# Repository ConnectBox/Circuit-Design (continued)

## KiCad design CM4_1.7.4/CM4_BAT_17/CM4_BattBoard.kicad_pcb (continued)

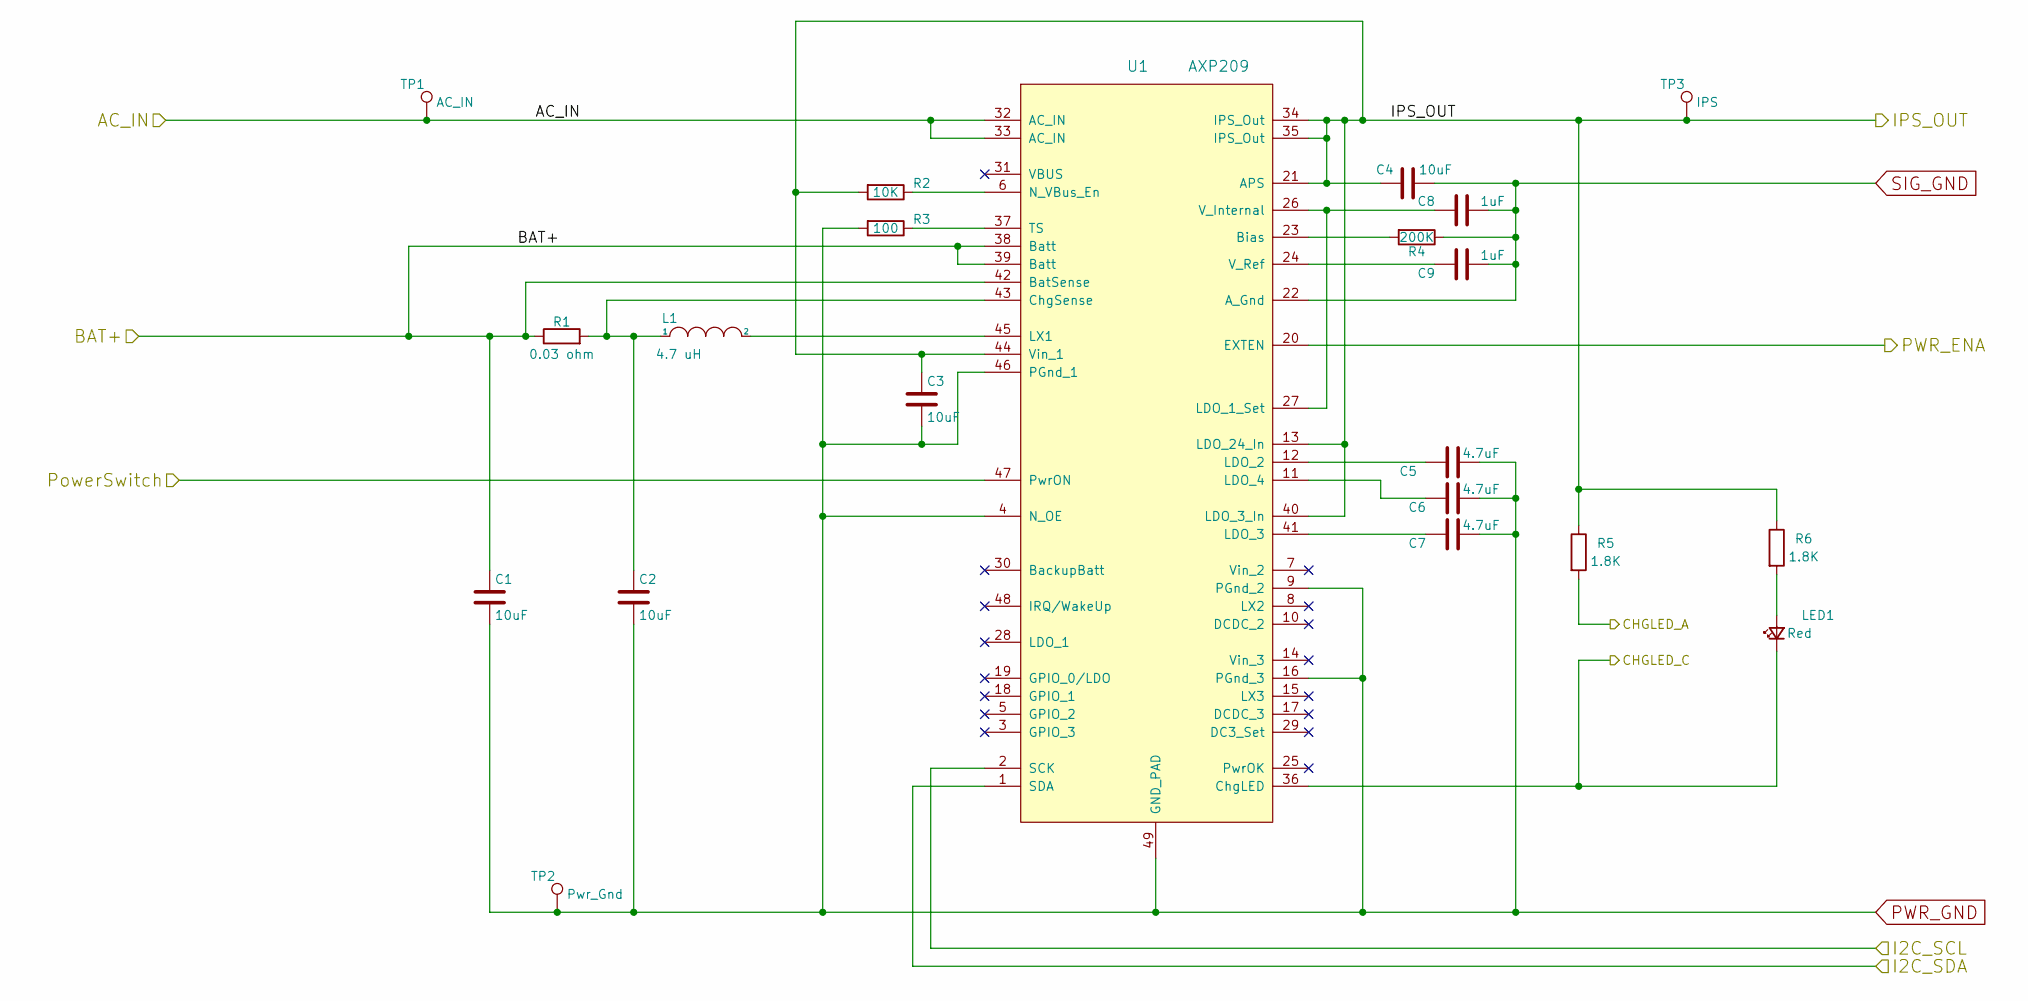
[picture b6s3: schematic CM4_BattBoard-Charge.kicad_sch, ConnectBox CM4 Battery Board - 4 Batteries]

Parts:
C1, C2, C3, C4: 10uF; C_0603_1608Metric; Manufacturer P/N C0603C106M9PACTU; DigiKey P/N 399-5504-1-ND
C5, C6, C7: 4.7uF; C_0603_1608Metric; Manufacturer P/N C0603C475K9PACTU; DigiKey P/N 399-3482-1-ND
C8, C9: 1uF; C_0603_1608Metric; Manufacturer P/N C0603C105K9PACTU; DigiKey P/N 399-7848-1-ND
L1: 4.7 uH; INDUCTOR_SMD_6x6-1; Manufacturer P/N NR6028T4R7M; DigiKey P/N 587-2100-1-ND
LED1: Red; LED_0603_1608Metric; Manufacturer P/N LTST-C191KRKT; DigiKey P/N 160-1447-1-ND
R1: 0.03 ohm; R_0805_2012Metric; Manufacturer P/N ERJ-6CWFR030V; DigiKey P/N P19207CT-ND
R2: 10K; R_0603_1608Metric; Manufacturer P/N RC0603FR-0710KL; DigiKey P/N 311-10.0KHRCT-ND
R3: 100; R_0603_1608Metric; Manufacturer P/N RC06-3FR-07100RL; DigiKey P/N 311-100HRCT-ND
R4: 200K; R_0603_1608Metric; Manufacturer P/N RC0603FR-07200KL; DigiKey P/N 311-200KHRCT-ND
R5, R6: 1.8K; R_0603_1608Metric; Manufacturer P/N RC0603FR-071K8L; DigiKey P/N 311-1.80KHRCT-ND
TP1: AC_IN; TestPoint_THTPad_D1.5mm_Drill0.7mm
TP2: Pwr_Gnd; TestPoint_THTPad_D1.5mm_Drill0.7mm
TP3: IPS; TestPoint_THTPad_D1.5mm_Drill0.7mm
U1: AXP209; UQFN-48-1EP_6x6mm_Pitch0.4mm_75; Manufacturer P/N AXP209

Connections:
/AC_IN: TP1.1, U1.32 (AC_IN), U1.33 (AC_IN); also elsewhere on the board
/CHGLED_A: R5.2; also elsewhere on the board
/CHGLED_C: LED1.1 (K), U1.36 (ChgLED); also elsewhere on the board
/Charge control/IPS_OUT: C3.1, C4.1, R2.2, R5.1, R6.1, TP3.1, U1.13 (LDO_24_In), U1.21 (APS), U1.34 (IPS_Out), U1.35 (IPS_Out), U1.40 (LDO_3_In), U1.44 (Vin_1); also elsewhere on the board
/I2C_SCL: U1.2 (SCK); also elsewhere on the board
/I2C_SDA: U1.1 (SDA); also elsewhere on the board
/PWR_ENA: U1.20 (EXTEN); also elsewhere on the board
/PowerSwitch: U1.47 (PwrON); also elsewhere on the board
unnamed: C2.1, L1.1, R1.2, U1.43 (ChgSense)
unnamed: C5.2, U1.12 (LDO_2)
unnamed: C6.2, U1.11 (LDO_4)
unnamed: C7.2, U1.41 (LDO_3)
unnamed: C8.2, U1.26 (V_Internal), U1.27 (LDO_1_Set)
unnamed: C9.2, U1.24 (V_Ref)
unnamed: L1.2, U1.45 (LX1)
unnamed: LED1.2 (A), R6.2
unnamed: R2.1, U1.6 (N_VBus_En)
unnamed: R3.1, U1.37 (TS)
unnamed: R4.2, U1.23 (Bias)
PWR_GND: C1.2, C2.2, C3.2, C5.1, C6.1, C7.1, R3.2, TP2.1, U1.4 (N_OE), U1.9 (PGnd_2), U1.16 (PGnd_3), U1.46 (PGnd_1), U1.49 (GND_PAD); also elsewhere on the board
SIG_GND: C4.2, C8.1, C9.1, R4.1, U1.22 (A_Gnd); also elsewhere on the board

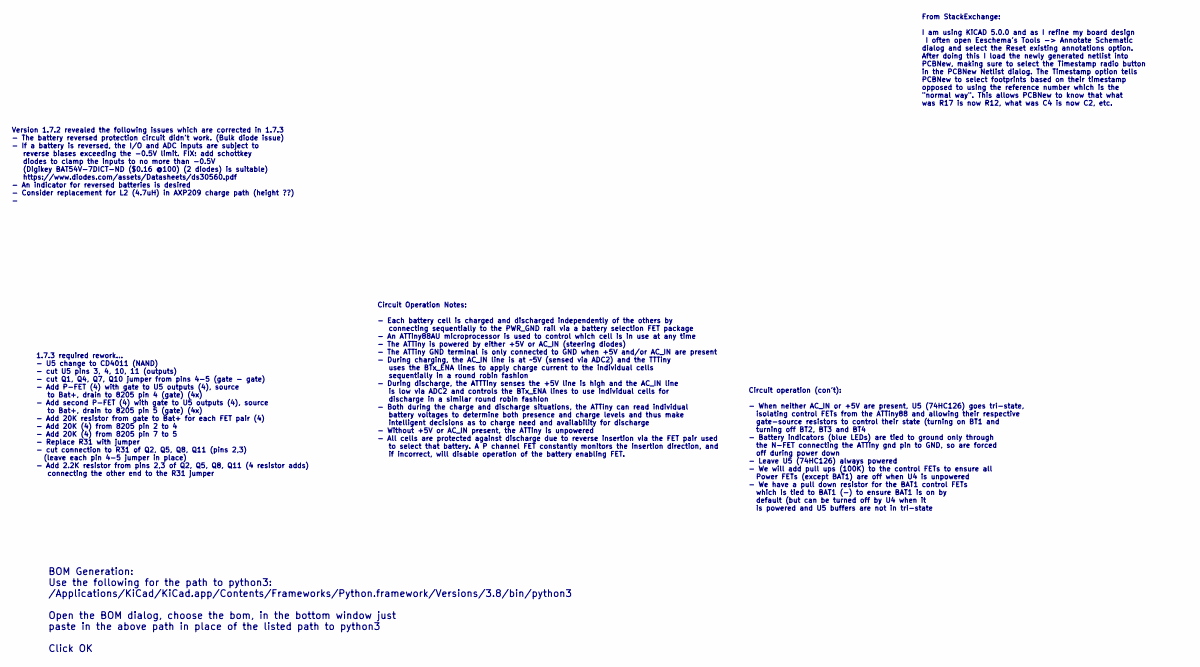
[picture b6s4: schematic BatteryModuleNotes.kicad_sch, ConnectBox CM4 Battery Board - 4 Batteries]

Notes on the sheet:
Version 1.7.2 revealed the following issues which are corrected in 1.7.3 - The battery reversed protection circuit didn't work. (Bulk diode issue) - If a battery is reversed, the I/O and ADC inputs are subject to reverse biases exceeding the -0.5V limit. FIX: add schottkey diodes to clamp the input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
1.7.3 required rework... - U5 change to CD4011 (NAND) - cut U5 pins 3, 4, 10, 11 (outputs) - cut Q1, Q4, Q7, Q10 jumper from pins 4-5 (gate - gate) - Add P-FET (4) with gate to U5 outputs (4), source to Bat+, drain to 8205 pin 4 (gate) (4x) - Add second P-FET (4) with gate to U5 outputs (4), source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
BOM Generation: Use the following for the path to python3: /Applications/KiCad/KiCad.app/Contents/Frameworks/Python.framework/Versions/3.8/bin/python3 Open the BOM dialog, choose the bom, in the bottom window just paste in the above path in place of the listed path to python3 Click OK
Circuit Operation Notes: - Each battery cell is charged and discharged independently of the others by connecting sequentially to the PWR_GND rail via a battery selection FET package - An ATTiny88AU microprocessor is used to control which cell is in use at any time - The ATTiny is powered by either 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
Circuit operation (con't): - When neither AC_IN or +5V are present, U5 (74HC126) goes tri-state, isolating control FETs from the ATTiny88 and allowing their respective gate-source resistors to control their state (turning on BT1 and turning off BT2, BT3 and BT4 - Battery indicators (blue LEDs) are 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
From StackExchange: I am using KiCAD 5.0.0 and as I refine my board design I often open Eeschema's Tools -> Annotate Schematic dialog and select the Reset existing annotations option. After doing this I load the newly generated netlist into PCBNew, making sure to select the Timestamp radio button i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

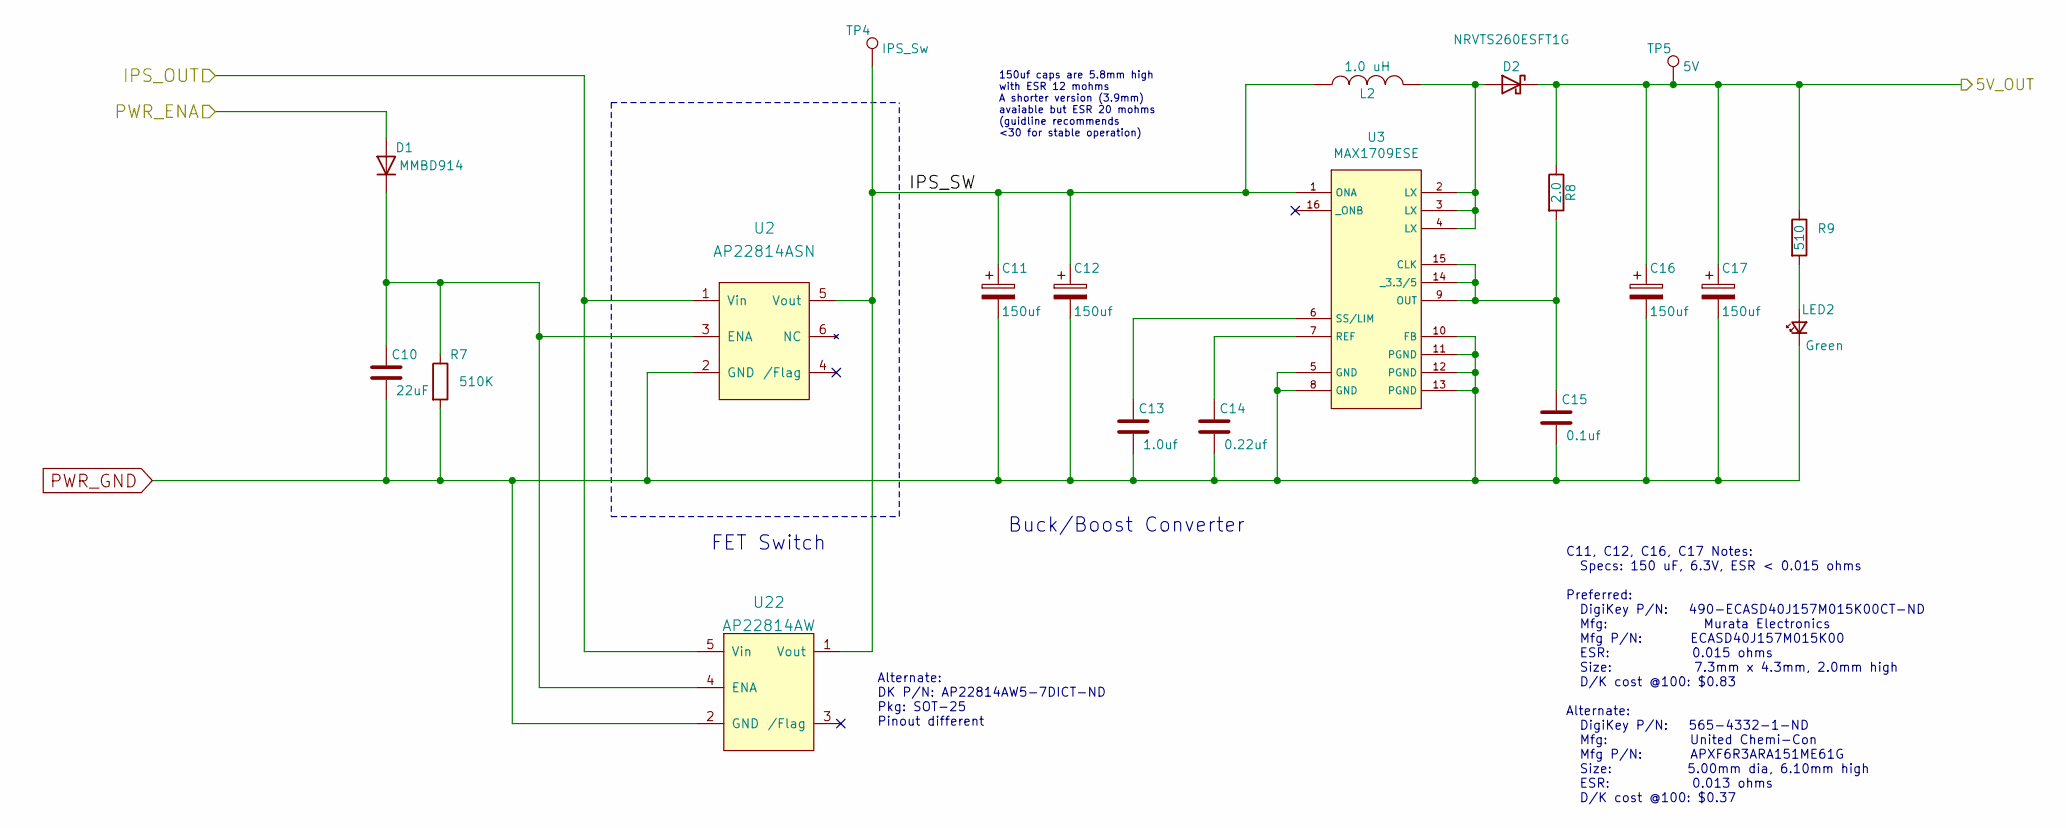
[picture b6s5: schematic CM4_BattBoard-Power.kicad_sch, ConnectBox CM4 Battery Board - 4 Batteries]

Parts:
C10: 22uF; C_0603_1608Metric; Manufacturer P/N CL10A226MQ8NRNC; DigiKey P/N 1276-1193-1-ND
C11, C12, C16, C17: 150uf; CAP_ECAS_SMD_dual; Manufacturer P/N ECASD40J157M015K00; DigiKey P/N 490-ECASD40J157M015K00CT-ND
C13: 1.0uf; C_0603_1608Metric; Manufacturer P/N C0603C105K9PACTU; DigiKey P/N 399-7848-1-ND
C14: 0.22uf; C_0603_1608Metric; Manufacturer P/N C0603C224K9PAC7867; DigiKey P/N 399-14969-1-ND
C15: 0.1uf; C_0603_1608Metric; Manufacturer P/N C0603C104K9PAC7867; DigiKey P/N 399-17575-1-ND
D1: MMBD914; D_SOT-23_ANK; Manufacturer P/N MMBD914LT1G; DigiKey P/N MMBD914LT1GOSCT-ND
D2: NRVTS260ESFT1G; SOD-123FL; Manufacturer P/N NRVTS260ESFT1G; DigiKey P/N NRVTS260ESFT1GOSCT-ND
L2: 1.0 uH; L_Taiyo-Yuden_MD-5050; Manufacturer P/N LQH5BPN1R0N38L; DigiKey P/N 490-16290-1-ND
LED2: Green; LED_0603_1608Metric; Manufacturer P/N LTST-C191KFKT; DigiKey P/N 160-1446-1-ND
R7: 510K; R_0603_1608Metric; Manufacturer P/N RC0603FR-07510KL; DigiKey P/N 311-510KHRCT-ND
R8: 2.0; R_0603_1608Metric; Manufacturer P/N RC0603FR-072RL; DigiKey P/N 311-2.00HRCT-ND
R9: 510; R_0603_1608Metric; Manufacturer P/N RC0603FR-07510RL; DigiKey P/N 311-510RHRCT-ND
TP4: IPS_Sw; TestPoint_THTPad_D1.5mm_Drill0.7mm
TP5: 5V; TestPoint_THTPad_D1.5mm_Drill0.7mm
U2: AP22814ASN; U-DFN2020-6; Manufacturer P/N AP22814ASN-7; DigiKey P/N AP22814ASN-7DICT-ND
U3: MAX1709ESE; SOP-16_3.9x9.9mm_P1.27mm; Manufacturer P/N MAX1709ESE
U22: AP22814AW; SOT-23-5; Manufacturer P/N AP22814AW5-7; DigiKey P/N AP22814AW5-7DICT-ND

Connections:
/+5V: C16.1, C17.1, D2.1 (K), R8.1, R9.1, TP5.1; also elsewhere on the board
/Charge control/IPS_OUT: U2.1 (Vin), U22.5 (Vin); also elsewhere on the board
/PWR_ENA: D1.2 (A); also elsewhere on the board
/Power/IPS_SW: C11.1, C12.1, L2.1, TP4.1, U2.5 (Vout), U3.1 (ONA), U22.1 (Vout)
unnamed: C10.1, D1.1 (K), R7.1, U2.3 (ENA), U22.4 (ENA)
unnamed: C13.1, U3.6 (SS/LIM)
unnamed: C14.1, U3.7 (REF)
unnamed: C15.1, R8.2, U3.9 (OUT), U3.14 (_3.3/5), U3.15 (CLK)
unnamed: D2.2 (A), L2.2, U3.2 (LX), U3.3 (LX), U3.4 (LX)
unnamed: LED2.2 (A), R9.2
PWR_GND: C10.2, C11.2, C12.2, C13.2, C14.2, C15.2, C16.2, C17.2, LED2.1 (K), R7.2, U2.2 (GND), U3.5 (GND), U3.8 (GND), U3.10 (FB), U3.11 (PGND), U3.12 (PGND), U3.13 (PGND), U22.2 (GND); also elsewhere on the board

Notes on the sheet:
FET Switch
Alternate: DK P/N: AP22814AW5-7DICT-ND Pkg: SOT-25 Pinout different
150uf caps are 5.8mm high with ESR 12 mohms A shorter version (3.9mm) avaiable but ESR 20 mohms (guidline recommends <30 for stable operation)
Buck/Boost Converter
C11, C12, C16, C17 Notes: Specs: 150 uF, 6.3V, ESR < 0.015 ohms Preferred: DigiKey P/N: 490-ECASD40J157M015K00CT-ND Mfg: Murata Electronics Mfg P/N: ECASD40J157M015K00 ESR: 0.015 ohms Size: 7.3mm x 4.3mm, 2.0mm high D/K cost @100: $0.83 Alternate: DigiKey P/N: 565-4332-1-ND Mfg: United Chemi-Con Mf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

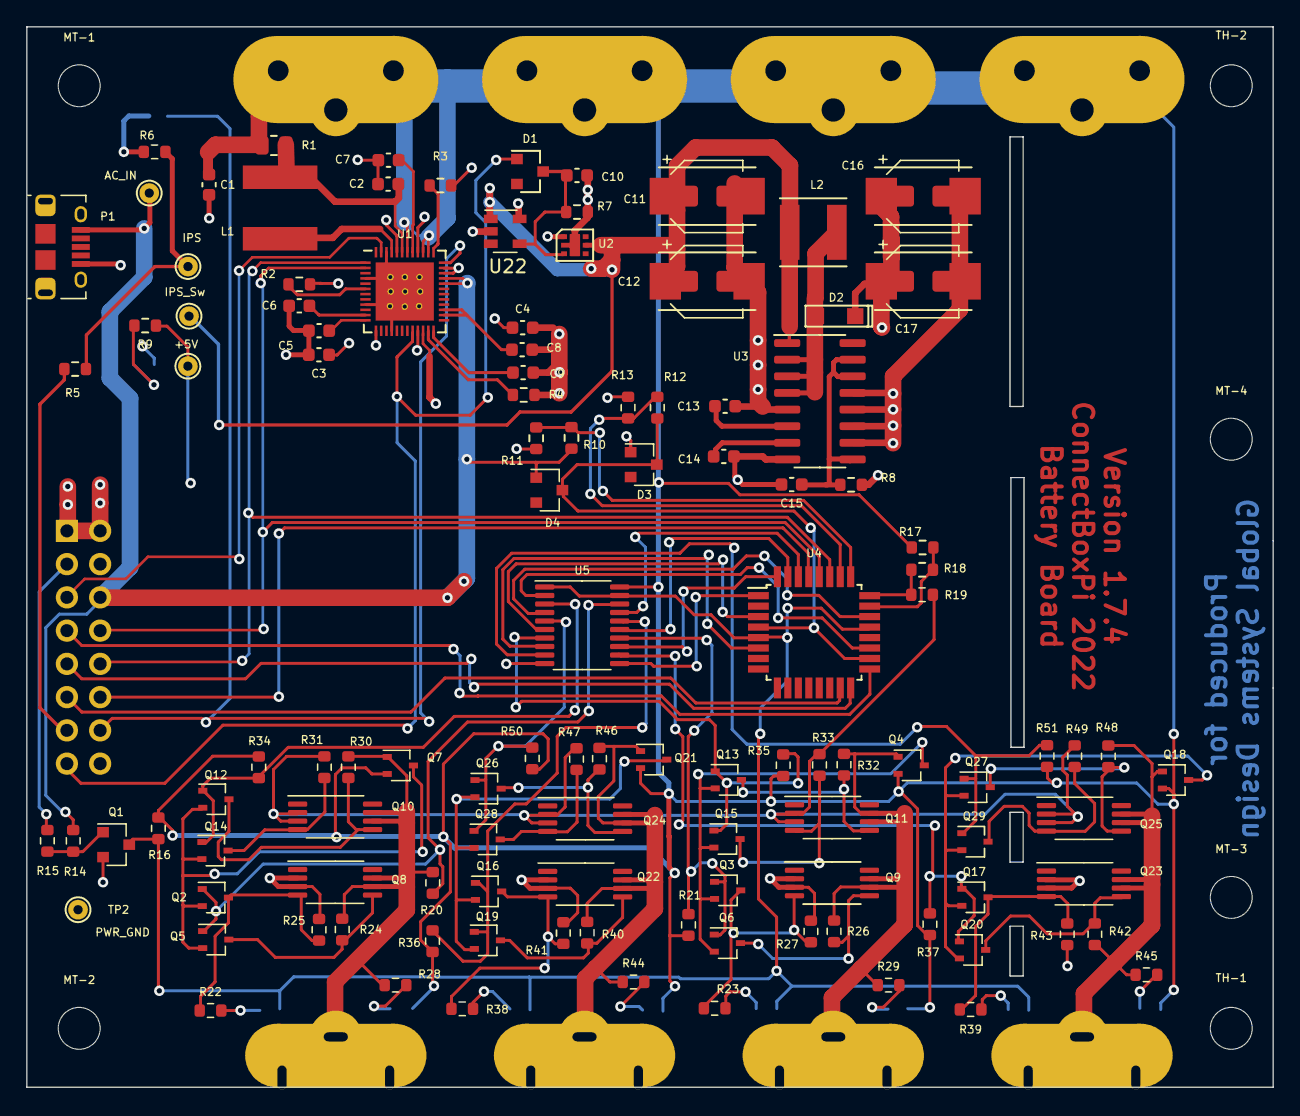
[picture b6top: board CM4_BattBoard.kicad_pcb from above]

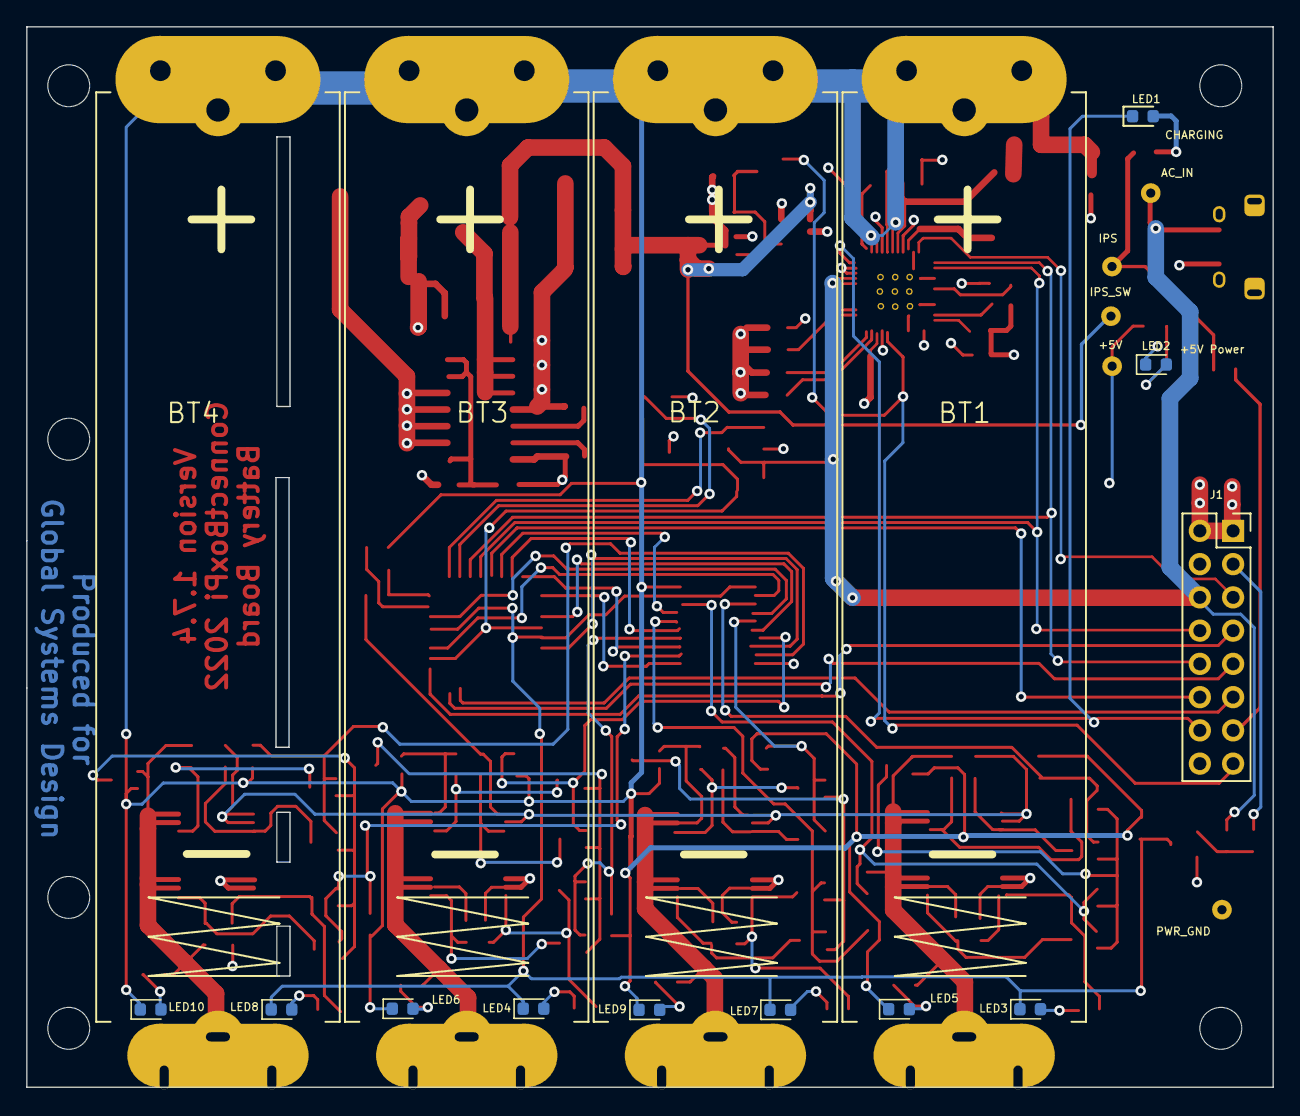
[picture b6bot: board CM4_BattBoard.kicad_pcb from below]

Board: 4 copper layers, 95.2 x 81.0 mm, 136 parts (15 on the bottom side), 90 nets.

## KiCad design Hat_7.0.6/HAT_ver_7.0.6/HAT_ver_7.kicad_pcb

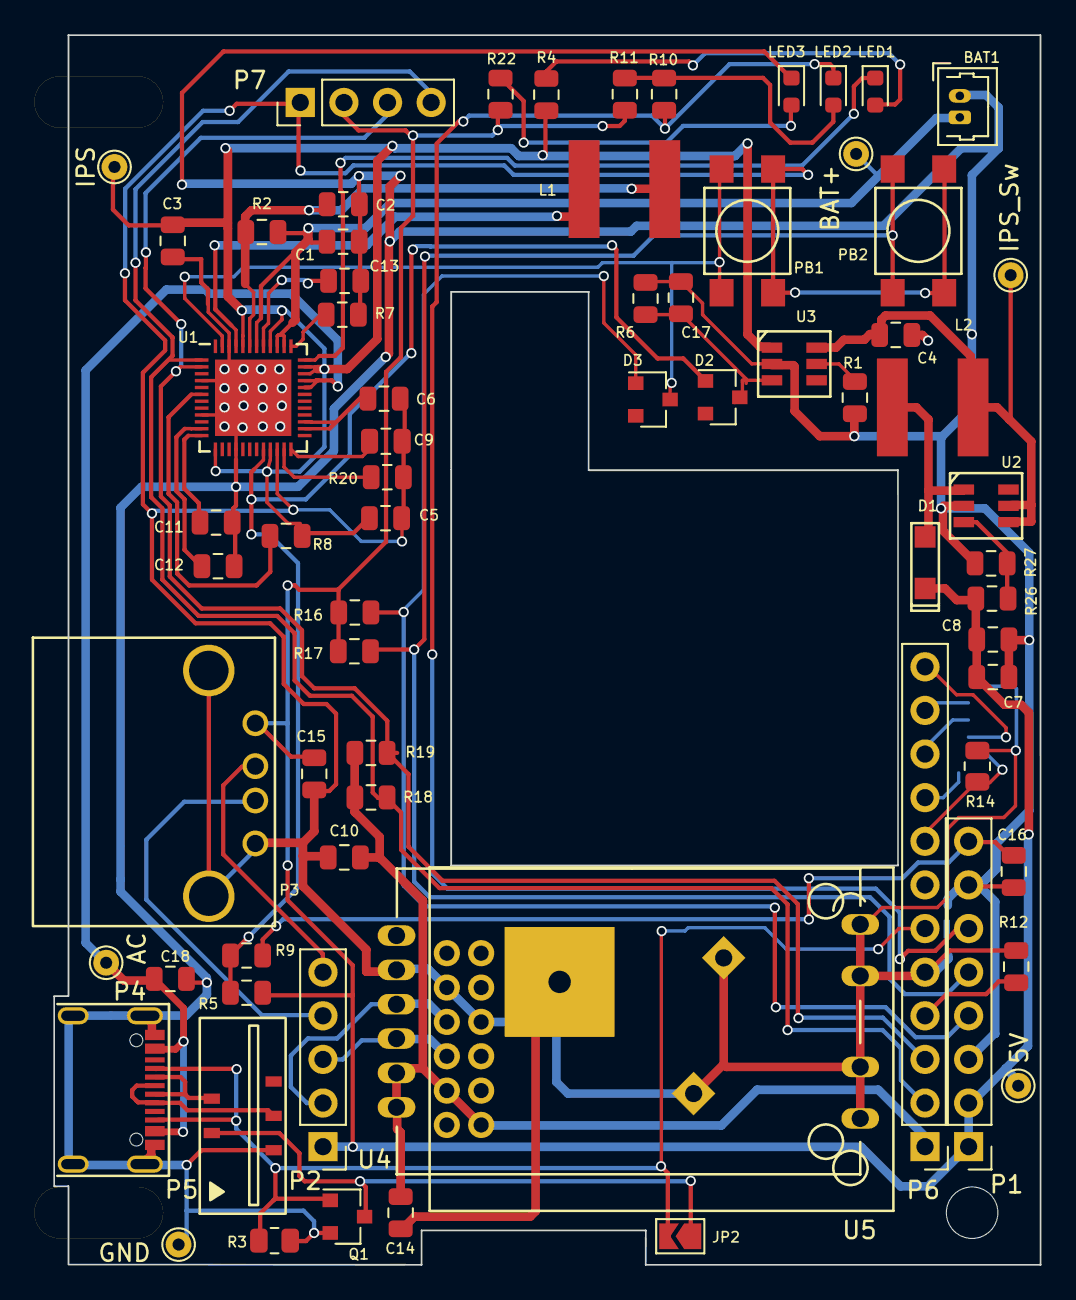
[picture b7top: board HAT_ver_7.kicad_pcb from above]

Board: 2 copper layers, 57.4 x 71.6 mm, 72 parts (1 on the bottom side), 48 nets.

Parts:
BAT1: Molex PicoBlade 53047-0210; Molex PicoBlade 53047-0210 - (swapped pins)
C1, C2, C3, C4, C5, C16: 10uF; C_0805_2012Metric
C6, C9, C10: 1uF; C_0805_2012Metric
C7, C8, C14, C15, C17, C18: 22uF; C_0805_2012Metric
C11, C12, C13: 4.7uF; C_0805_2012Metric
D1: NRVTS260ESFT1G; SOD-123FL
D2, D3: MMBD914; D_SOT-23_ANK
JP1: Jumper_NC_Small; NetConnect-50
JP2: SolderJumper_2_Open; SolderJumper-2_P1.3mm_Open_TrianglePad1.0x1.5mm
L1, L2: 4.7 uH; INDUCTOR_SMD_6x6-1
LED1: Red; LED_0603_1608Metric
LED2: Amber; LED_0603_1608Metric
LED3: Green; LED_0603_1608Metric
P1: Conn_01x08; PinHeader_1x08_P2.54mm_Vertical
P2: Conn_01x05; PinHeader_1x05_P2.54mm_Vertical
P3: USB_A_1; USB_A
P4: USB-C; USB-C-GCT
P5: Conn_01x05; SFW5S-2STE1LF
P6: Conn_01x12; PinHeader_1x12_P2.54mm_Vertical
P7: Conn_01x04; PinHeader_1x04_P2.54mm_Vertical
P8: Conn_01x06; SFW6R-1STE1LF
PB1, PB2: SPST-PUSH; SW-TL3305
Q1: 2N7002; SOT-23
R1: 162; R_0805_2012Metric
R2: 0.03 ohm; R_0805_2012Metric
R3, R8, R16, R17: 10K; R_0805_2012Metric
R4: 1.8K; R_0805_2012Metric
R5: 51K; R_0805_2012Metric
R6: 220K; R_0805_2012Metric
R7: 100; R_0805_2012Metric
R9, R10, R11, R22: 1K; R_0805_2012Metric
R12, R14, R18, R19: 2.2K; R_0805_2012Metric
R20, R26: 200K; R_0805_2012Metric
R27: 27.0K; R_0805_2012Metric
TP1: AC_IN; TestPoint_THTPad_D1.5mm_Drill0.7mm
TP2: Bat+; TestPoint_THTPad_D1.5mm_Drill0.7mm
TP3: Gnd; TestPoint_THTPad_D1.5mm_Drill0.7mm
TP4: IPS; TestPoint_THTPad_D1.5mm_Drill0.7mm
TP5: 5V; TestPoint_THTPad_D1.5mm_Drill0.7mm
TP6: IPS_Sw; TestPoint_THTPad_D1.5mm_Drill0.7mm
U1: AXP209; UQFN-48-1EP_6x6mm_Pitch0.4mm_75
U2: MT3608; SOT-23-6a
U3: MIC2019; SOT-23-6a
U4: HC-R8812AF1; HC-R8812AU2-th-1
U5: F12ASUM13-W2

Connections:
/3v3: C10.1, C14.1, P6.1, R18.2, R19.2, U4.1 (PDN), U4.2 (3.3V), U5.6 (3.3V), U5.11 (3.3V)
/3v3a: P6.9, P8.6
/5V_OUT: C7.1, C8.1, C15.2, D1.1 (K), P1.1, P1.2, P2.1, P3.1 (VCC), P7.2, R5.1, R11.1, R16.2, R17.2, R22.1, R26.1, TP5.1
/AC_IN: C18.1, P4.A4/B9 (Power), P4.B4/A9 (Power), TP1.1, U1.32 (AC_IN), U1.33 (AC_IN)
/A_GND: C5.1, C6.1, C9.1, C10.2, C14.2, C15.1, JP1.1, P3.4 (GND), P3.5 (shield), P6.5, P7.1, P8.1, PB1.2, PB2.2, R12.2, R14.2, R20.1, U1.22 (A_Gnd), U4.5 (GND), U4.7 (GND), U4.9 (GND), U4.10 (GND), U4.12 (GND), U4.13 (GND), U4.14 (GND), U4.15 (GND), U5.3 (GND), U5.8 (GND)
/IPS_OUT: C3.1, C5.2, R4.1, R8.2, TP4.1, U1.13 (LDO_24_In), U1.21 (APS), U1.34 (IPS_Out), U1.35 (IPS_Out), U1.40 (LDO_3_In), U1.44 (Vin_1), U3.1 (Vin)
/PA0: JP2.2 (B), P4.A5 (CC1), P4.B5 (CC2), P6.6, Q1.1 (G), R3.1
/PA3: P6.8, P8.5, R14.1
/PG6: D3.1 (K), PB1.1, U1.47 (PwrON)
/PG7: P1.5, PB2.1, R17.1
/PG11: P6.4, R12.1
/Power control/BAT+: BAT1.1, C1.1, R2.1, TP2.1, U1.38 (Batt), U1.39 (Batt), U1.42 (BatSense)
/Power control/EXT_EN: D2.2 (A), R5.2, R9.1, U1.20 (EXTEN)
/SCL: P6.3, P7.3, R19.1, U1.2 (SCK)
/SDA: P6.2, P7.4, R18.1, U1.1 (SDA)
/SPI0_CLK: P6.12, P8.4
/SPI0_MISO: P6.11, P8.2
/SPI0_MOSI: P6.10, P8.3
GND: BAT1.2, C1.2, C2.2, C3.2, C4.2, C7.2, C8.2, C11.1, C12.1, C13.1, C16.1, C17.2, C18.2, JP1.2, LED3.1 (K), P1.3, P1.7, P4.1 (Shell), P4.A1/B12 (GND), P4.B1/A12 (GND), P5.1, Q1.2 (S), R1.2, R3.2, R6.2, R7.2, R27.2, TP3.1, U1.4 (N_OE), U1.9 (PGnd_2), U1.16 (PGnd_3), U1.46 (PGnd_1), U1.49 (GND_PAD), U2.2 (GND), U3.2 (GND)
unnamed: C2.1, L1.1, R2.2, U1.43 (ChgSense)
unnamed: C4.1, L2.1, TP6.1, U2.4 (EN), U2.5 (IN), U3.6 (Vout)
unnamed: C6.2, U1.26 (V_Internal), U1.27 (LDO_1_Set)
unnamed: C9.2, U1.24 (V_Ref)
unnamed: C11.2, U1.12 (LDO_2)
unnamed: C12.2, U1.11 (LDO_4)
unnamed: C13.2, U1.41 (LDO_3)
unnamed: C16.2, P1.8, R9.2
unnamed: C17.1, D2.1 (K), R6.1, U3.3 (ENA)
unnamed: D1.2 (A), L2.2, U2.1 (LX)
unnamed: D3.2 (A), P1.4, R16.1
unnamed: JP2.1 (A), P5.2, Q1.3 (D)
unnamed: L1.2, U1.45 (LX1)
unnamed: LED1.1 (K), U1.36 (ChgLED)
unnamed: LED1.2 (A), R4.2
unnamed: LED2.1 (K), P1.6, R10.2
unnamed: LED2.2 (A), R10.1, R11.2
unnamed: LED3.2 (A), R22.2
unnamed: P2.2, U4.4 (DP+), U5.9 (DP+)
unnamed: P2.3, U4.3 (DM-), U5.10 (DM-)
unnamed: P2.4, P3.3 (D+)
unnamed: P2.5, P3.2 (D-)
unnamed: P4.A6 (D+), P4.B6 (D+), P5.3
unnamed: P4.A7 (D-), P4.B7 (D-), P5.4
unnamed: R1.1, U3.5 (ILim)
unnamed: R7.1, U1.37 (TS)
unnamed: R8.1, U1.6 (N_VBus_En)
unnamed: R20.2, U1.23 (Bias)
unnamed: R26.2, R27.1, U2.3 (FB)

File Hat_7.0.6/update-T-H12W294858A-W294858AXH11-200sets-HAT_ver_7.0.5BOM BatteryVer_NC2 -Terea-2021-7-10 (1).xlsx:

200-220sets | 200sets | Comment from PCBWay |  | Changed… from last production run | Designator | Quantity | Value | Manufacturer | Manufacturer Part Number or Seed SKU | Link
0.385 | 77 |  |  |  | BAT1 | 1 |  | Molex | 530470210 | https://www.digikey.com/products/en?keywords=530470210
0.0165 | 9.9 |  |  |  | C10 C9 C6 | 3 | 1 uF | KEMET | C0805C105K8PACTU | https://www.digikey.com/products/en/capacitors/ceramic-capac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
0.033 | 19.8 |  |  |  | C11 C12 C13 | 3 | 4.7 uF | Samsung Electro-Mechanics | CL21B475KPFNNNE | https://www.digikey.com/products/en/capacitors/ceramic-capac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
0.11 | 132 |  |  |  | C4 C16 C1 C2 C5 C3 | 6 | 10 uF | Samsung Electro-Mechanics | CL21A106MPFNNNE | https://www.digikey.com/products/en/capacitors/ceramic-capac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
0.11 | 132 |  |  |  | C7 C8 C14 C15 C17 C18 | 6 | 22 uF | KEMET | C0805C226M8PAC7800 | https://www.digikey.com/products/en/capacitors/ceramic-capac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
0.33 | 66 | V2F6-M3/H 7-10work days |  |  | D1 | 1 |  | ON Semiconductor | NRVTS260ESFT1G | https://www.digikey.com/products/en/discrete-semiconductor-p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
0.055 | 22 |  |  | add D3 | D2 D3 | 2 |  | ON Semiconductor | MMBD914LT1G | https://www.digikey.com/product-detail/en/on-semiconductor/M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
0.275 | 110 |  |  |  | L2 L1 | 2 |  | Taiyo Yuden | NR6028T4R7M | https://www.digikey.com/products/en/inductors-coils-chokes/f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
0.055 | 11 |  |  |  | LED1 | 1 |  | Lite-On Inc. | LTST-C191KRKT | https://www.digikey.com/products/en/optoelectronics/led-indi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
0.055 | 11 |  |  |  | LED2 | 1 |  | Lite-On Inc. | LTST-C191KFKT | https://www.digikey.com/products/en/optoelectronics/led-indi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
0.055 | 11 |  |  |  | LED3 | 1 |  | Lite-On Inc. | LTST-C191KGKT | https://www.digikey.com/products/en?keywords=160-1446-1-nd
0.11 | 22 |  |  |  | P1 | 1 | Conn 1x8 | Sullins Connector Solutions | PPPC081LFBN-RC | https://www.digikey.com/products/en?keywords=PPPC081LFBN-RC
0.066 | 13.2 |  |  | remove P6 | P2 | 1 | Conn 1x5 | Sullins Connector Solutions | PPPC051LFBN-RC | https://www.digikey.com/products/en?keywords=PPPC051LFBN-RC
0.506 | 101.2 | 7-10work days |  |  | P3 | 1 | USB-A | On Shore Technology Inc. | USB-A1HSW6 | https://www.digikey.com/products/en?keywords=USB-A1HSW6
0.55 | 0 |  |  | P4 changed to USB-C |  | 0 |  | Amphenol ICC (FCI) | 10118194-0001LF | https://www.digikey.com/products/en/connectors-interconnects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
0.836 | 167.2 | 7-10work days |  | NEW P4 | P4 | 1 | USB-C | GCT | USB4105-GF-A | https://www.digikey.com/en/products/detail/gct/USB4105-GF-A/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
0.517 | 103.4 | P&S MOQ:4pcs 7-10work days |  | NEW P5 | P5 | 1 | Flex 1x5 | Amphenol | SFW5S-2STE1LF | https://www.digikey.com/en/products/detail/amphenol-icc-fci/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
0.165 | 33 |  |  | NEW P6 | P6 | 1 | Conn 1x12 | Sullins Connector Solutions | PPPC121LFBN-RC | https://www.digikey.com/en/products/detail/sullins-connector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
0.066 | 13.2 |  |  |  | P7 | 1 | Conn 1x4 | Sullins Connector Solutions | PPPC041LFBN-RC | https://www.digikey.com/products/en?keywords=PPPC041LFBN-RC
1.012 | 202.4 | 7-10work days |  | NEW P8 | P8 | 1 | Flex 1x6 | Amphenol | SFW6R-2STE1LF | https://www.digikey.com/en/products/detail/amphenol-icc-fci/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
0.33 | 132 | digikey125pcs 2-3 weeks |  |  | PB1 PB2 | 2 |  | E-Switch | TL3305AF260QG | https://www.digikey.com/products/en/switches/tactile-switche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
0.121 | 24.2 | 7-10work days |  | NEW Q1 | Q1 | 1 | 2N7002 | Toshiba Semiconductor | T2N7002BK,LM | https://www.digikey.com/en/products/detail/toshiba-semicondu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
0.0077 | 1.54 |  |  |  | R1 | 1 | 162 ohm | Yageo | RC0805FR-07162R | https://www.digikey.com/products/en/resistors/chip-resistor-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
0.0077 | 6.16 |  |  | Add R3 | R16 R17 R8 R3 | 4 | 10K | Yageo | RC0805FR-0710KL | https://www.digikey.com/products/en/resistors/chip-resistor-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
0.0077 | 6.16 |  |  | Add R14 | R19 R18 R12 R14 | 4 | 2.2K | Yageo | RC0805FR-072K2L | https://www.digikey.com/products/en/resistors/chip-resistor-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
0.44 | 88 | 7-10work days |  |  | R2 | 1 | 0.03 ohm | Panasonic Electronic Components | ERJ-6CWFR030V | https://www.digikey.com/products/en/resistors/chip-resistor-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
0.0077 | 6.16 |  |  | Remove R3, R13 | R22 R9 R11 R10 | 4 | 1K | Yageo | RC0805FR-071KL | https://www.digikey.com/products/en/resistors/chip-resistor-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
0.0077 | 3.08 |  |  |  | R26 R20 | 2 | 200K | Yageo | RC0805FR-07200KL | https://www.digikey.com/products/en/resistors/chip-resistor-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
0.0077 | 1.54 |  |  |  | R27 | 1 | 27K | Yageo | RC0805FR-0727KL | https://www.digikey.com/products/en/resistors/chip-resistor-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
0.0077 | 1.54 |  |  |  | R4 | 1 | 1.8K | Yageo | RC0805FR-071K8L | https://www.digikey.com/products/en/resistors/chip-resistor-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
0.0077 | 1.54 |  |  |  | R5 | 1 | 51K | Yageo | RC0805FR-0751KL | https://www.digikey.com/products/en?keywords=311-51.0KCRCT-ND
0.0077 | 1.54 |  |  |  | R6 | 1 | 220K | Yageo | RC0805FR-07220KL | https://www.digikey.com/products/en/resistors/chip-resistor-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
0.0077 | 1.54 |  |  |  | R7 | 1 | 100 ohm | Yageo | RC0805FR-07100RL | https://www.digikey.com/products/en/resistors/chip-resistor-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
 |  | DNP |  | Remove SW1 |  | 0 |  | C&K | OS102011MA1QN1 | https://www.digikey.com/products/en?keywords=OS102011MA1QN1
2.2 | 440 |  |  |  | U1 | 1 |  | X-Powers | AXP209 | https://www.kynix.com/Detail/120792/AXP209.html
0.165 | 33 |  |  |  | U2 | 1 |  | AEROSEMI | MT3608 | www.kynix.com/Detail/584537/MT3608.html
0.55 | 110 |  |  |  | U3 | 1 |  | Microchip Technology | MIC2019YM6-TR | https://www.digikey.com/products/en/integrated-circuits-ics/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
 |  | Customer provide |  |  | U5 U4 | 1 |  | High Cloud | HC-R8812AF1
 |  |  | total
 |  |  |  |  | U5 U4
 | 2115.3

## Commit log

2018-07-31 New Circuit Folder 4.7
2018-07-31 Fix Commit
2018-07-31 Updated 4.7 Hat
2018-07-31 Completed upload of design
2019-07-08 Version 5.1 PCB for Case 5.1
2019-10-29 Updated Latest Versions
    Version 5.1.1
    Version 6.0.1
2019-11-23 New revision for injection molded case
2020-02-10 Updated Circuit board based on molded case design
2021-07-24 Added new hat with flex for MegaVoice
2022-04-12 Hat Changes including Version 2.0
2022-04-14 Updated to second protype release
2022-04-14 Updated to 183 release which fixes some traces to close to cutouts
2022-11-26 Rename KiCad 7.0.6 folder for consistency
2022-11-26 Initial release of CB-CM4 circuit documents
2023-06-06 Updated hat schematics
2025-01-07 Added Model R Design Files
    Circuit Design Files for Model R
2025-03-09 Version 8.3.1 for removable battery design
